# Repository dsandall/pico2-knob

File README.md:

# pico2-knob

A small **wireless BLE control puck**: a knob (rotary encoder), an OLED screen, and three
buttons, on a round Ø80 mm 2-layer PCB, powered by a **nice!nano v2** (nRF52840) + LiPo.

> Name is legacy — it started as an RP2350/Pico 2 board, then moved to the nice!nano for
> wireless. This repo is the hardware (schematic + layout), a rough mechanical mockup, and
> `firmware/` — currently just bring-up firmware (Rust/Embassy, UF2) for the soldered board:
> LED heartbeat plus encoder/button events over USB serial. No screen, battery or BLE yet.

## Open it
`hardware/pico2-knob.kicad_pro` in **KiCad 10**. The schematic embeds its symbols and the
board embeds its footprints, so it opens standalone; `lib/marbastlib` (nice!nano sym/fp) and
the project lib-tables are included so libraries resolve cleanly too.

## Board summary
- **MCU:** nice!nano v2 — mounted on the **back**, on female sockets, USB-C facing the top
  rim (charge/flash; the device is otherwise sealed and battery-powered over BLE).
- **Encoder:** Alps EC11 w/ pushbutton, shaft at the puck center.
- **Buttons:** 3 × 6 mm tactile (SW_PUSH_6mm), in an arc below the knob.
- **Display:** ER-OLED1.12-2 (SH1107) on a 20-pin ribbon connector (J3, ER-CON20HT-1),
  driven as 4-wire SPI. Panel VPP comes from a 12 V boost (U2, MC34063) off +BATT,
  gated by Q1 from `12V_EN`.
- **Power:** LiPo on a JST-PH (J2) → nice!nano on-board charger (BAT+/GND). No power switch
  (nRF52 sleeps at µA; add an inline slide switch in VBAT if you want true-off).
- **Outline:** Ø80 mm round (bumped up from Ø74 for fab edge-clearance on the nano pads).
- 2-layer, GND pours both sides, 55 tracks, 0 vias. **DRC: 0 errors.**

## Net / GPIO map (nRF52 pads)
| Signal | nice!nano pad |
|--------|---------------|
| Encoder A / B / SW | P0.09 / P0.10 / P1.11 (pads 24 / 23 / 22) |
| Buttons 1 / 2 / 3 | P0.31 / P0.02 / P1.15 (pads 17 / 19 / 20) |
| OLED DC / SCLK / SDI | P0.06 / P0.08 / P0.17 (pads 1 / 2 / 5) |
| OLED RES / CS | P0.22 / P0.24 (pads 7 / 8), 10 kΩ pull-ups (R2/R6) |
| 12V_EN (panel rail) | P1.06 (pad 12), active low — R8 pulls Q1's gate to +BATT |
| Power | 3V3 (pad 16), GND, BAT+ → +BATT |

## For the reviewer 👀
This layout was **script-generated** (see `scripts/`) and auto-routed (freerouting), then
hand-touched at the encoder. Please sanity-check freely — a few notes:
- **2 DRC items are intentionally downgraded to warnings:** `pth_inside_courtyard` between
  the back-side socketed nano and the front-side encoder courtyard. The nano sits ~8.5 mm
  below the board on sockets, so there's no real clash — but please confirm you agree.
- The encoder signal nets stack collinearly under the nano; they're hand-routed
  (`scripts/manual_route.py`) and S2's GND return is a manual trace into the south pour
  (`scripts/fix_s2.py`).
- **Not yet done:** mounting features (holes/standoffs) — coming after the enclosure.
- Pin assignment is flexible (nRF52 GPIOs are interchangeable) — happy to remap for cleaner
  routing if you see a better arrangement.

## Layout of this repo
- `hardware/` — KiCad 10 project (schematic, PCB, lib-tables)
- `lib/marbastlib/` — nice!nano symbol + footprint (trimmed to what's used)
- `scripts/` — generators: `gen_sch.py`, `gen_pcb.py`, routing helpers; `*.sh` render/ERC/DRC
- `cad/` — FreeCAD mechanical mockup (`mockup.py`) + component STEP models (`step/`)
- `build/pico2-knob.pdf` — quick-look: schematic + routed layout

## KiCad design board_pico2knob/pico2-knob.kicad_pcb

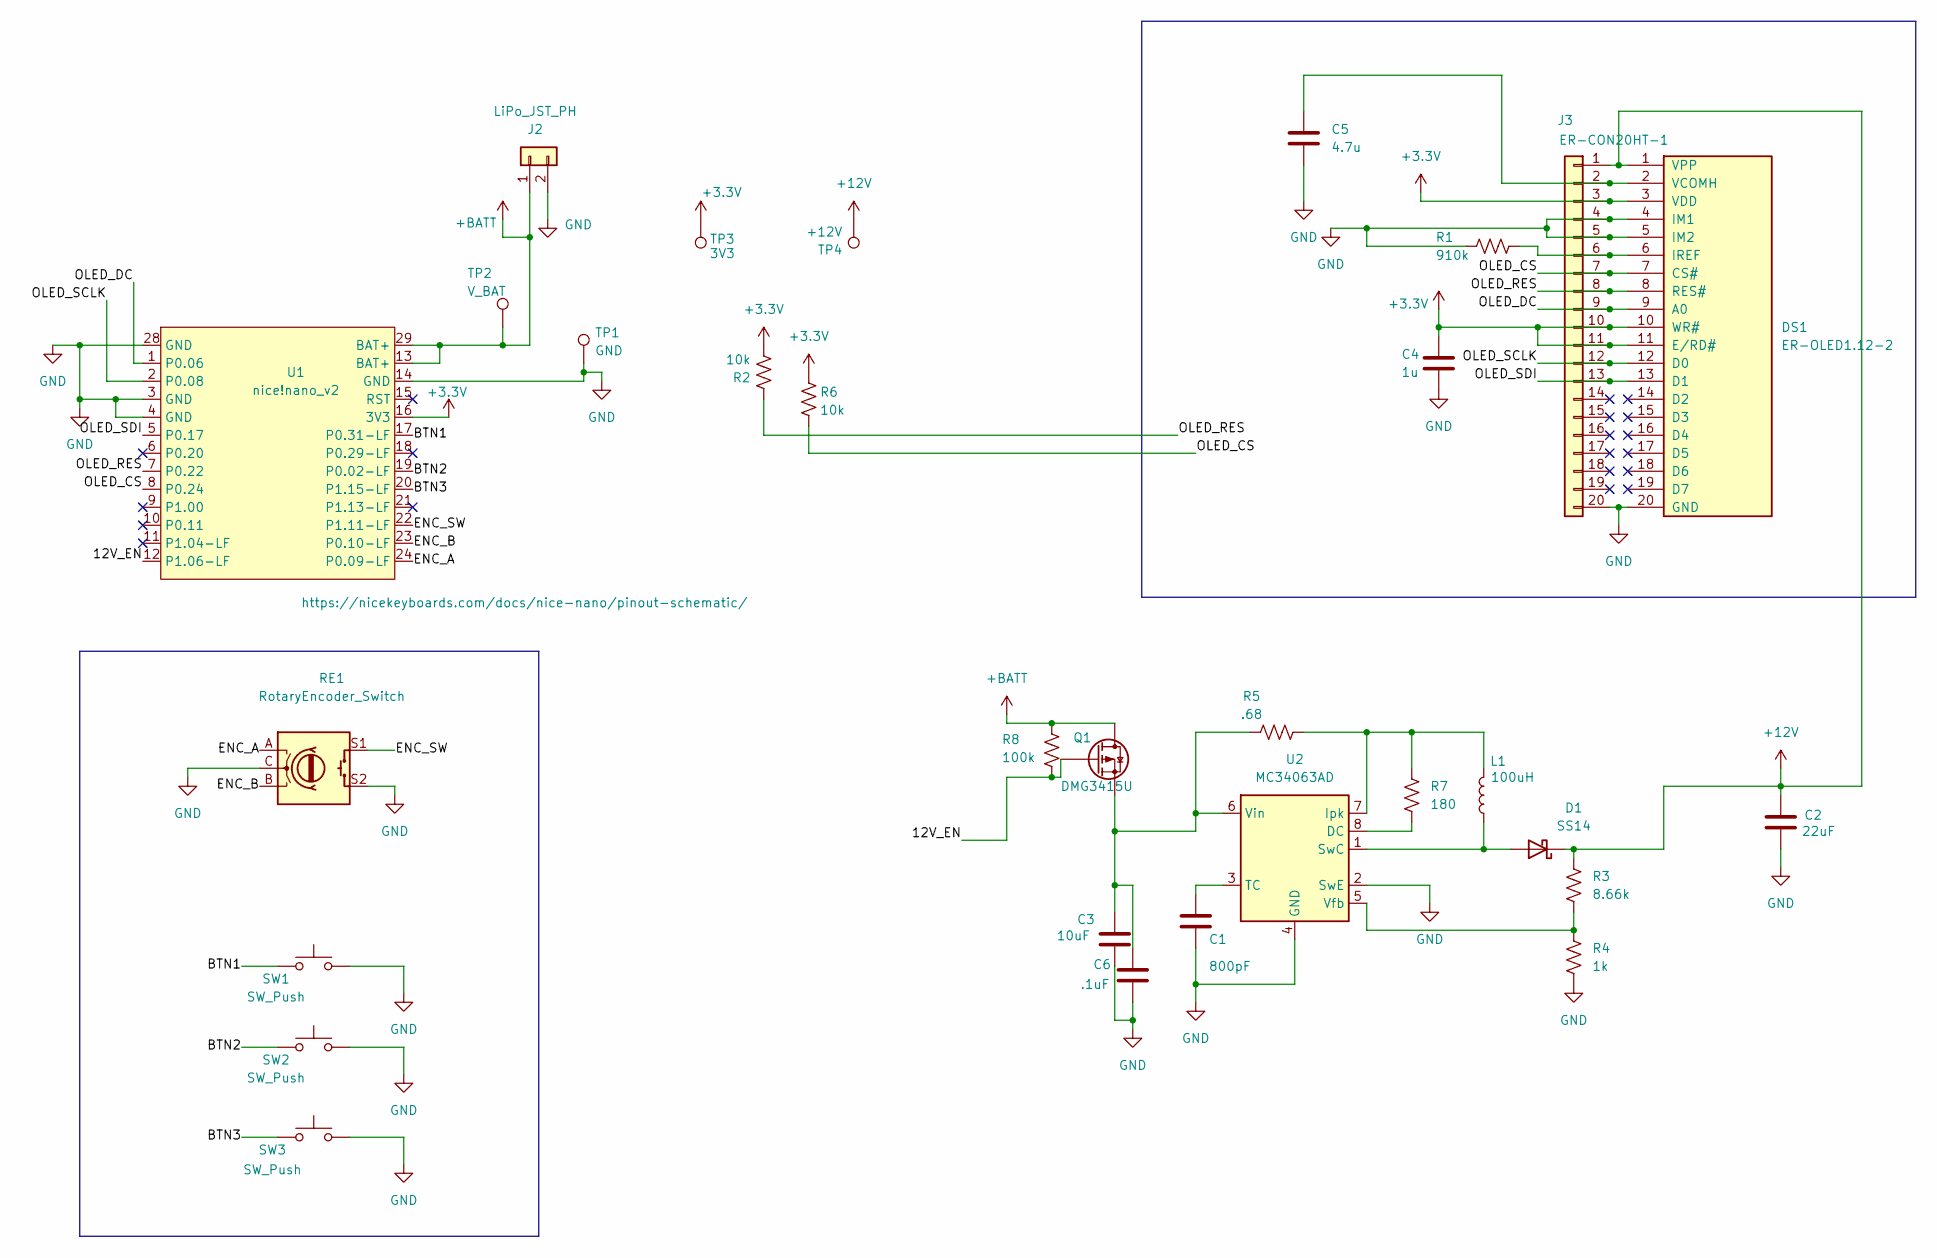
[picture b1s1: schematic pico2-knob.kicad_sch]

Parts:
C1: 800pF; C_1206_3216Metric; MFRPN CC1206KRX7R9BB681
C2: 22uF; C_1210_3225Metric; MFRPN GRM32ER61E226KE15L
C3: 10uF; C_1206_3216Metric; MFRPN GRM31CR61E106KA12L
C4: 1u; C_1206_3216Metric; MFRPN CL31B105KBHNNNE
C5: 4.7u; C_1206_3216Metric; MFRPN GRM31CR61E475KA12L
C6: .1uF; C_1206_3216Metric; MFRPN GRM31CR61E106KA12L
D1: SS14; D_SMA; MFRPN SS14-E3/61T
DS1: ER-OLED1.12-2; MFRPN ER-OLED1.12-2W
J2: LiPo_JST_PH; JST_PH_S2B-PH-K_1x02_P2.00mm_Horizontal; MFRPN S2B-PH-K-S
J3: ER-CON20HT-1; MFRPN ER-CON20HT-1
L1: 100uH; L_12x12mm_H6mm; MFRPN SRR1260-101M
Q1: DMG3415U; SOT-23; MFRPN DMG3415U-7
R1: 910k; R_Axial_DIN0207_L6.3mm_D2.5mm_P7.62mm_Horizontal; MFRPN MFR-25FBF52-910K
R2, R6: 10k; R_Axial_DIN0207_L6.3mm_D2.5mm_P7.62mm_Horizontal; MFRPN MFR-25FBF52-10K
R3: 8.66k; R_Axial_DIN0207_L6.3mm_D2.5mm_P7.62mm_Horizontal; MFRPN CFR-25JB-52-R68
R4: 1k; R_Axial_DIN0207_L6.3mm_D2.5mm_P7.62mm_Horizontal; MFRPN MFR-25FBF52-1K
R5: .68; R_Axial_DIN0207_L6.3mm_D2.5mm_P7.62mm_Horizontal; MFRPN MFR-25FBF52-8K66
R7: 180; R_Axial_DIN0207_L6.3mm_D2.5mm_P7.62mm_Horizontal; MFRPN CFR-25JB-52-R68
R8: 100k; R_Axial_DIN0207_L6.3mm_D2.5mm_P7.62mm_Horizontal; MFRPN CFR-25JB-52-R68
RE1: RotaryEncoder_Switch; RotaryEncoder_Alps_EC11E-Switch_Vertical_H20mm; MFRPN EC11E15244G1
SW1, SW2, SW3: SW_Push; SW_PUSH_6mm; MFRPN SKHHAKA010
TP1: GND; TestPoint_Pad_D1.5mm
TP2: V_BAT; TestPoint_Pad_D1.5mm
TP3: 3V3; TestPoint_Pad_D1.5mm
TP4: +12V; TestPoint_Pad_D1.5mm
U1: nice!nano_v2; nice_nano_AH_Reversible; MFRPN nice!nano_v2
U2: MC34063AD; SOIC-8_3.9x4.9mm_P1.27mm; MFRPN MC34063ADR2G

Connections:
+3.3V: C4.2, DS1.3 (VDD), DS1.10 (WR#), DS1.11 (E/RD#), J3.3, J3.10, J3.11, R2.1, R6.1, TP3.1 (1_1), U1.16 (3V3)
+12V: C2.1, D1.1 (K), DS1.1 (VPP), J3.1, R3.1, TP4.1 (1_1)
+BATT: J2.1, Q1.D, R8.1, TP2.1 (1_1), U1.13 (BAT+), U1.29 (BAT+)
/12V_EN: Q1.G, R8.2, U1.12 (P1.06-LF)
/BTN1: SW1.1, U1.17 (P0.31-LF)
/BTN2: SW2.1, U1.19 (P0.02-LF)
/BTN3: SW3.1, U1.20 (P1.15-LF)
/ENC_A: RE1.A, U1.24 (P0.09-LF)
/ENC_B: RE1.B, U1.23 (P0.10-LF)
/ENC_SW: RE1.S1, U1.22 (P1.11-LF)
/OLED_CS: DS1.7 (CS#), J3.7, R6.2, U1.8 (P0.24)
/OLED_DC: DS1.9 (A0), J3.9, U1.1 (P0.06)
/OLED_RES: DS1.8 (RES#), J3.8, R2.2, U1.7 (P0.22)
/OLED_SCLK: DS1.12 (D0), J3.12, U1.2 (P0.08)
/OLED_SDI: DS1.13 (D1), J3.13, U1.5 (P0.17)
GND: C1.2, C2.2, C3.2, C4.1, C5.2, C6.2, DS1.4 (IM1), DS1.5 (IM2), DS1.20 (GND), J2.2, J3.4, J3.5, J3.20, R1.2, R4.2, RE1.C, RE1.S2, SW1.2, SW2.2, SW3.2, TP1.1 (1_1), U1.3 (GND), U1.4 (GND), U1.14 (GND), U1.28 (GND), U2.2 (SwE), U2.4 (GND)
unnamed: D1.2 (A), L1.1, U2.1 (SwC)
unnamed: C5.1, DS1.2 (VCOMH), J3.2
unnamed: DS1.6 (IREF), J3.6, R1.1
unnamed: R7.2, U2.8 (DC)
unnamed: L1.2, R5.2, R7.1, U2.7 (Ipk)
unnamed: C1.1, U2.3 (TC)
unnamed: R3.2, R4.1, U2.5 (Vfb)
unnamed: C3.1, C6.1, Q1.S, R5.1, U2.6 (Vin)

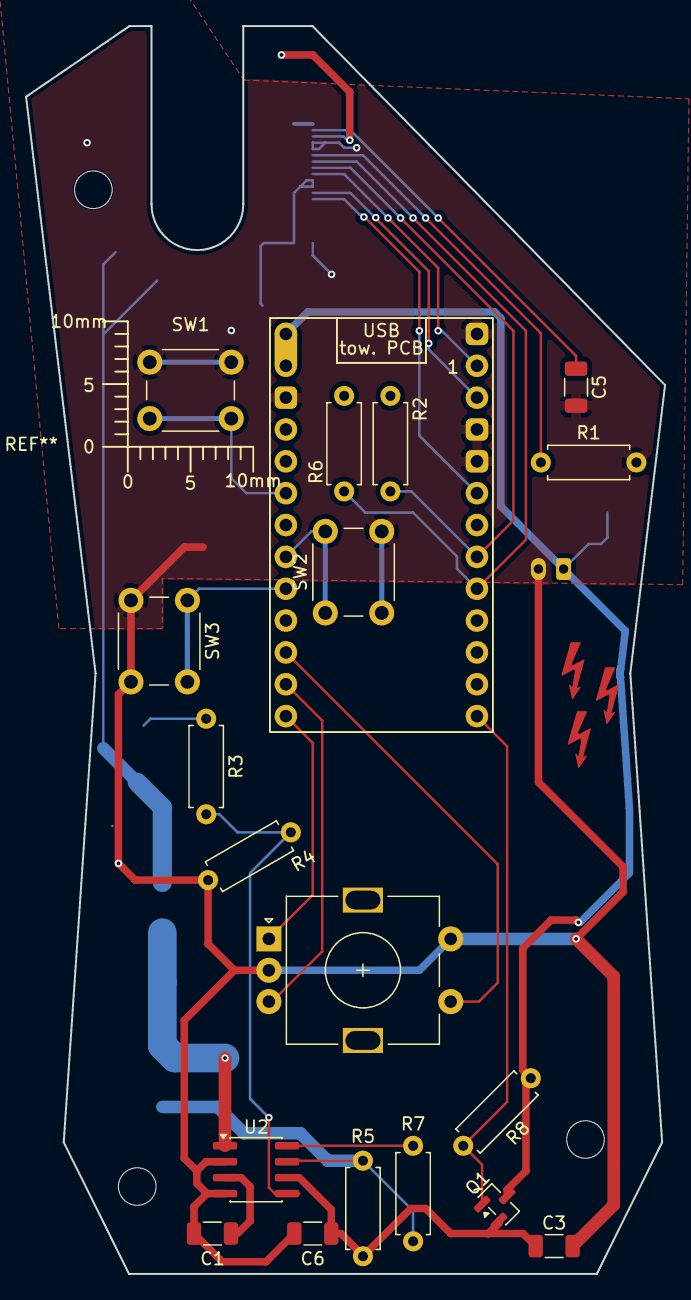
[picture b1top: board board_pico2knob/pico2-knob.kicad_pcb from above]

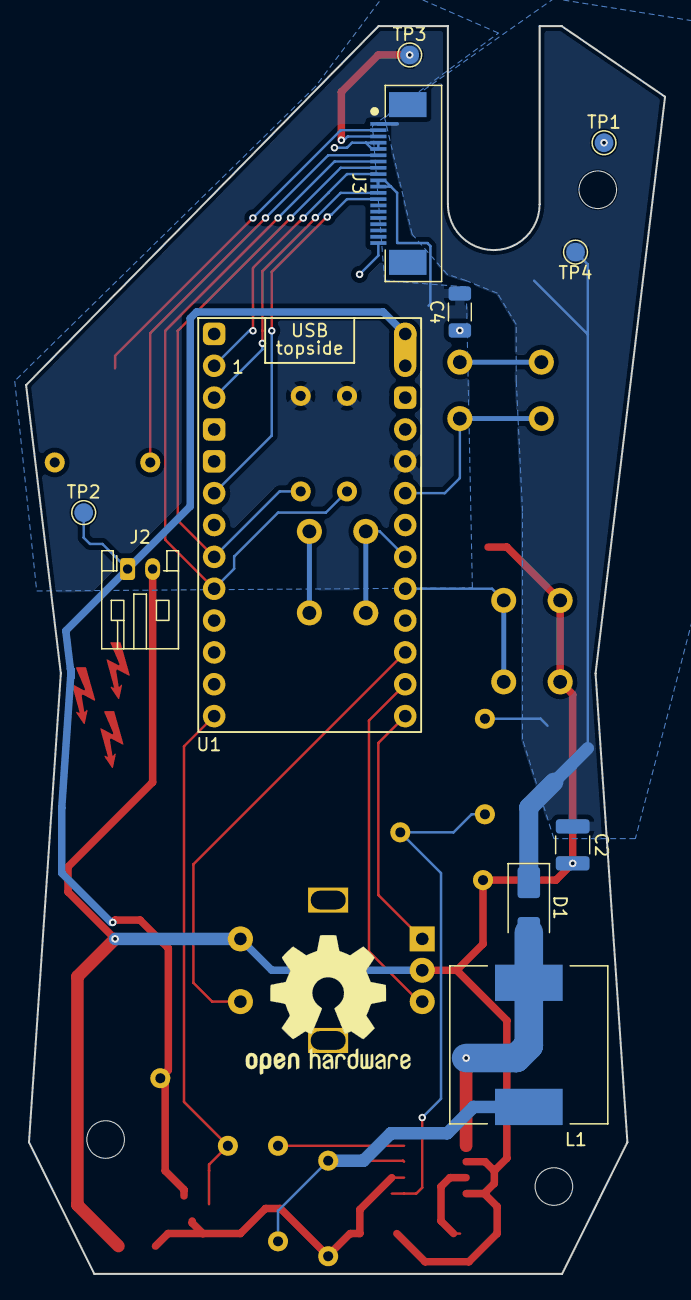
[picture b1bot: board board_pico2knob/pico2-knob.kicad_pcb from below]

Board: 2 copper layers, 51.0 x 99.5 mm, 29 parts (11 on the bottom side), 24 nets.

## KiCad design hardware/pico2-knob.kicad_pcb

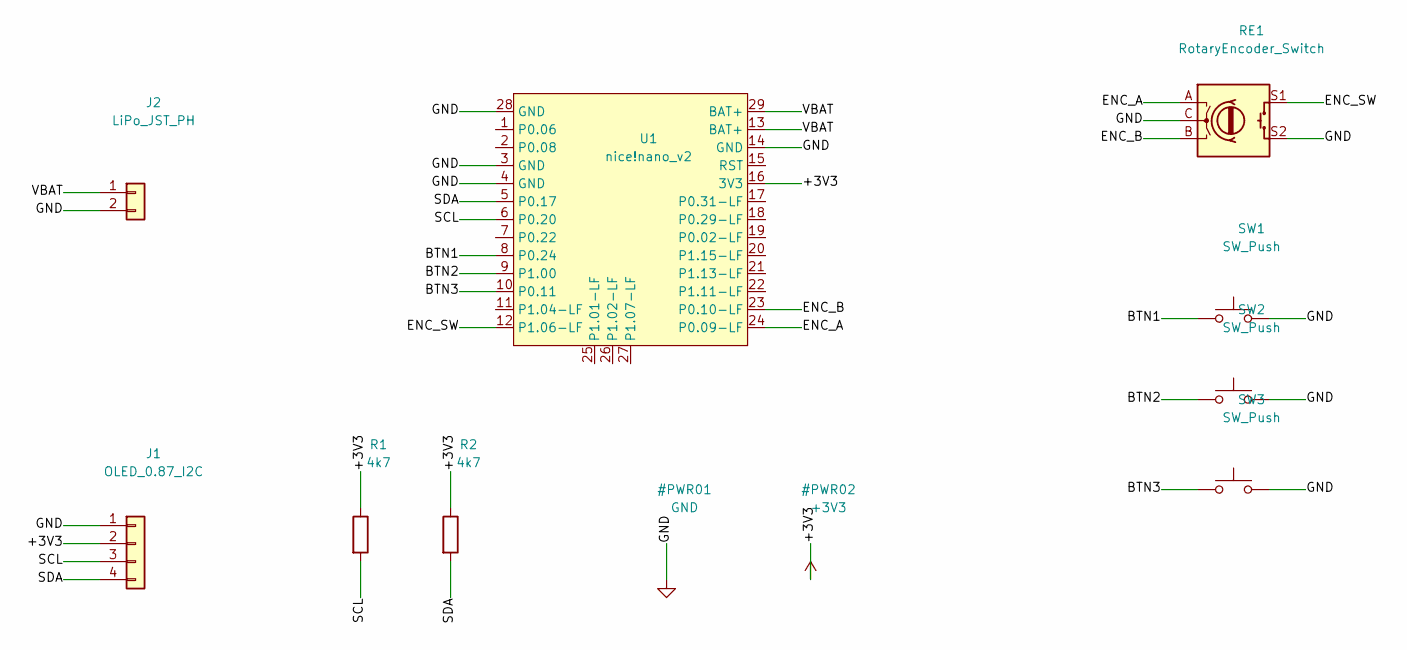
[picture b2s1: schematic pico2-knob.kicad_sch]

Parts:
J1: OLED_0.87_I2C; PinSocket_1x04_P2.54mm_Vertical
J2: LiPo_JST_PH; JST_PH_S2B-PH-K_1x02_P2.00mm_Horizontal
R1, R2: 4k7; R_0603_1608Metric
RE1: RotaryEncoder_Switch; RotaryEncoder_Alps_EC11E-Switch_Vertical_H20mm
SW1, SW2, SW3: SW_Push; SW_PUSH_6mm
U1: nice!nano_v2; nice_nano_AH_Reversible

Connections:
+3V3: J1.2, R1.1, R2.1, U1.16 (3V3)
BTN1: SW1.1, U1.8 (P0.24)
BTN2: SW2.1, U1.9 (P1.00)
BTN3: SW3.1, U1.10 (P0.11)
ENC_A: RE1.A, U1.24 (P0.09-LF)
ENC_B: RE1.B, U1.23 (P0.10-LF)
ENC_SW: RE1.S1, U1.12 (P1.06-LF)
GND: J1.1, J2.2, RE1.C, RE1.S2, SW1.2, SW2.2, SW3.2, U1.3 (GND), U1.4 (GND), U1.14 (GND), U1.28 (GND)
SCL: J1.3, R1.2, U1.6 (P0.20)
SDA: J1.4, R2.2, U1.5 (P0.17)
VBAT: J2.1, U1.13 (BAT+), U1.29 (BAT+)

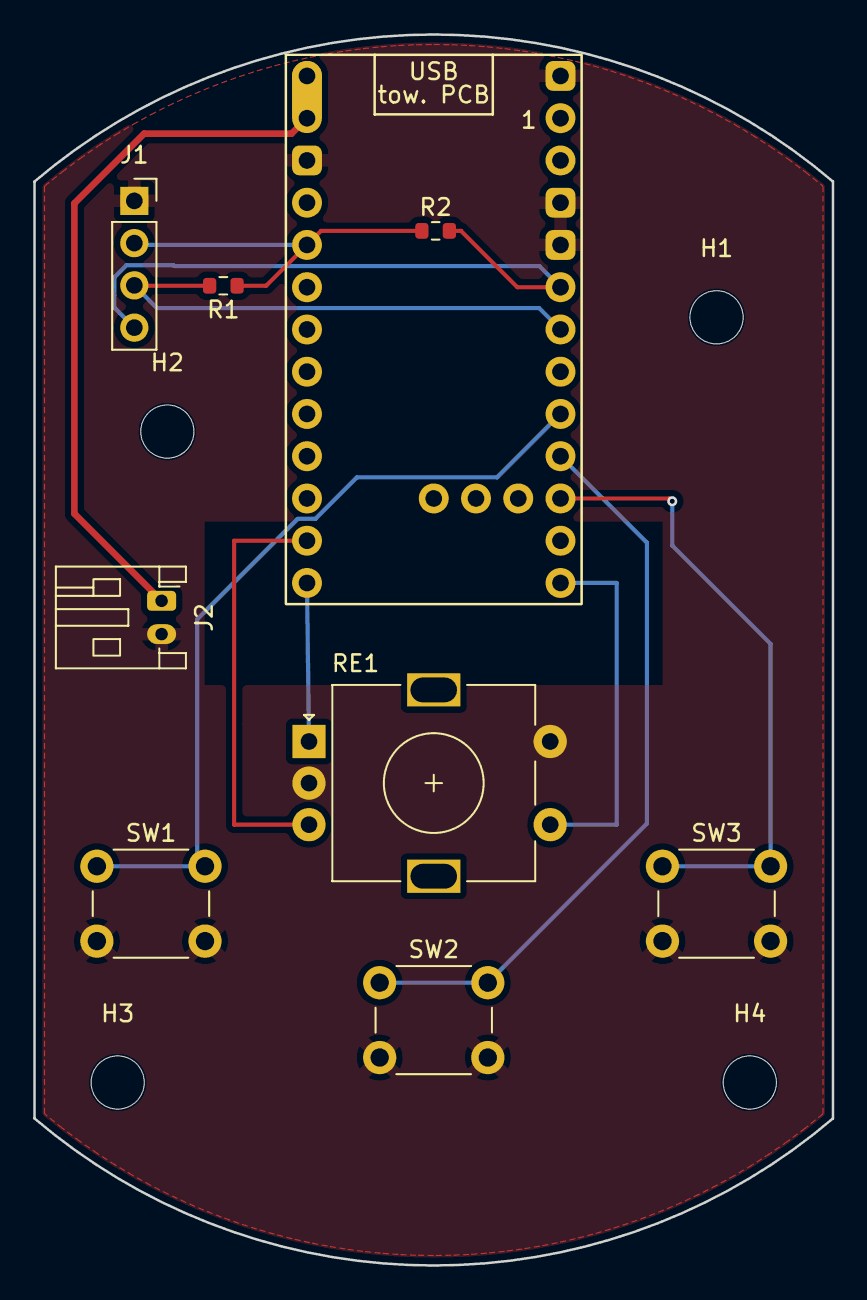
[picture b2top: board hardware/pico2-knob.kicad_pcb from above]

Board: 2 copper layers, 48.0 x 74.0 mm, 13 parts (1 on the bottom side), 11 nets.

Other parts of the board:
H1, H2, H3, H4: MountingHole_3.2mm_M3

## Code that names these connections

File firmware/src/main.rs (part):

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//! |-----------|----------|-----|---------------------------------------------|
//! | LED       | P0.15    |  -  | on-module blue LED, active high             |
//! | VCC_EN    | P0.13    |  -  | nice!nano load switch: high = 3V3 pad live  |
//! | ENC_A     | P0.09    | 24  | NFC pin, freed via `nfc-pins-as-gpio`       |
//! | ENC_B     | P0.10    | 23  | likewise                                    |
//! | ENC_SW    | P1.11    | 22  |                                             |
//! | BTN1      | P0.31    | 17  |                                             |
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/// How long the orientation test pattern stays up at boot.
const SPLASH: Duration = Duration::from_millis(1500);

const SWITCH_NAMES: [&str; 4] = ["BTN1", "BTN2", "BTN3", "ENC_SW"];

const HELP: &str = concat!(
    "\r\ncommands: ? help | p pins | d next view (or hold the knob and turn it)\r\n",
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                let mut line: String<128> = String::new();
                let _ = write!(
                    line,
                    "pins ENC_A={} ENC_B={}",
                    enc_a.is_high() as u8,
                    enc_b.is_high() as u8
                );
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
